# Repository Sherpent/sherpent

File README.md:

# Sherpent – Équipe #3
## S.H.E.R.P.E.N.T.
Système
Hybride
Exploratoire
Robotique
Prototypé
Et
Navigation
Tout-terrain

## 🌐 Projet: Sherpent – Robot Tout-Terrain Inspiré des Serpents

**Membres de l'équipe :**
- **Nathan Lachapelle** (lacn1101)
- **Émile Raymond** (raye1901)
- **Gabriel Grondin** (grog1401)
- **Mathieu Durand** (durm1207)
- **Renaud Gagnon** (gegr1618)
- **Maxime Boucher** (boom0704)

---

## 🔬 Contexte

Le projet Sherpent vise à concevoir et prototyper un véhicule tout-terrain s’inspirant des mouvements ondulatoires d’un serpent pour se déplacer. Les serpents utilisent leurs centaines de vertèbres et leurs muscles pour glisser sur diverses surfaces (‎terre, bois, vitre, sable, etc.), ce qui leur confère une capacité passe-partout. Ce type de locomotion est idéal pour des missions d’exploration terrestre ou pour évoluer dans des environnements extraterrestres hostiles.

L'étude des mouvements naturels de ces reptiles servira de base à la conception du robot Sherpent.

---

## 🎯 Objectifs du Projet

- **Robot articulé :** Le robot comprendra des joints articulés permettant des mouvements ondulatoires.
- **Actionneurs et capteurs :** Intégration d’actionneurs et de capteurs pour permettre un contrôle précis des mouvements.
- **Contrôle autonome :** Le robot fonctionnera de manière autonome, sans dépendance à des fils ou sources externes.
- **Langage Python :** Utilisation de Python pour une partie du code contrôlant le robot.
- **Applications potentielles :** Exploration terrestre ou exploration d’environnements extraterrestres.

---

## 📅 Livrables Attendues
Le projet sera développé en utilisant la méthodologie Agile, avec des livrables majeurs prévus à la fin de chaque sprint de 3 semaines :

| **Dates**           | **Livrables Importants**                  |
|---------------------|------------------------------------------|
| 22 janvier 2025     | Preuve de concept simple                |
| 12 février 2025    | PCB montés et débuggés                 |
| 26 février 2025    | Contrôle du prototype                  |
| 26 mars 2025        | Phase de test du prototype              |
| 11 avril 2025       | Rapport et prototype final              |

---

## 📊 Analyse Sommaire de Faisabilité

**Compétences :** L’équipe possède une expertise multidisciplinaire en robotique :
- Compétences en électronique, mécanique et informatique.

**Ressources matérielles :** 
- Accès à du matériel et des installations telles que machines-outils, composants électroniques, et équipements de prototypage.

**Budget :** Les coûts supplémentaires seront partagés ou répartis selon les membres qui conserveront les matériaux au terme du projet.

**Conclusion :** Compte tenu des compétences, du matériel disponible et des ressources temporelles, l’équipe juge ce projet réalisable dans les délais impartis.

---

## 🔄 Planification Sommaire

1. **Organisation de l’équipe :**
   - Division en trois sections : électrique, mécanique, et informatique.
   - Collaboration interdépendante pour surmonter les embûches.

2. **Gestion de Projet :**
   - Utilisation de GitHub pour gérer le code, les fichiers, et la planification.
   - Réunion hebdomadaire chaque mercredi pour faire le point sur les avancements et problèmes.

3. **Développement Agile :**
   - Livrables précis à la fin de chaque sprint de 3 semaines.

---

## 🔧 Utilisation de GitHub

1. **Structure du Répertoire :**
   ```
   Sherpent/
   ├── elec/       # Fichiers électroniques (PCB, schémas, etc.)
   ├── mec/        # Fichiers mécaniques (CAD, modèles 3D, etc.)
   ├── code/       # Fichiers de code (Python, firmware, etc.)
   └── docs/       # Documentation et rapports
   ```

2. **Outils GitHub :**
   - **Issues :** Pour suivre les problèmes et défis.
   - **Projets :** Pour gérer les tâches et la planification Agile.
   - **Pull Requests :** Pour réviser et intégrer les changements.

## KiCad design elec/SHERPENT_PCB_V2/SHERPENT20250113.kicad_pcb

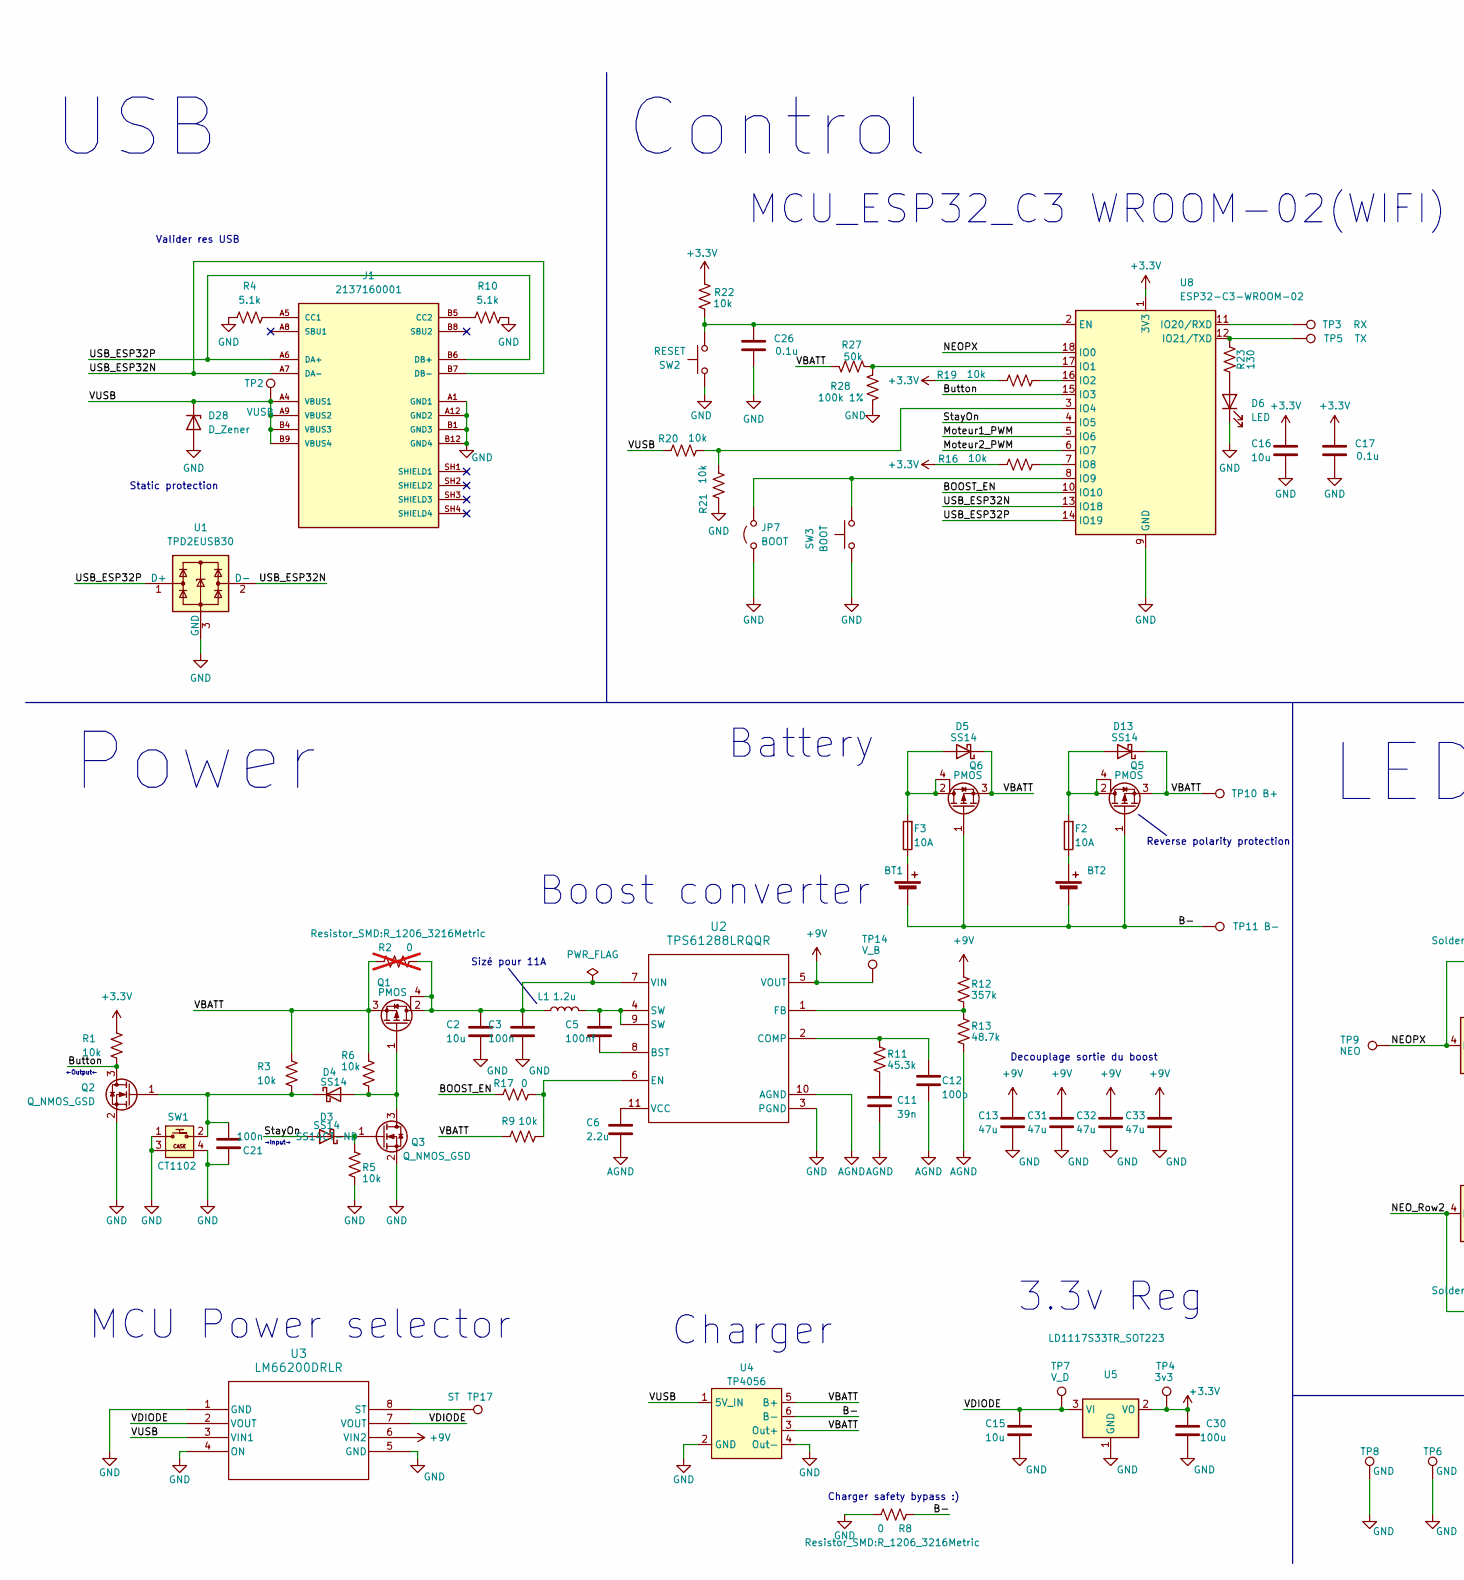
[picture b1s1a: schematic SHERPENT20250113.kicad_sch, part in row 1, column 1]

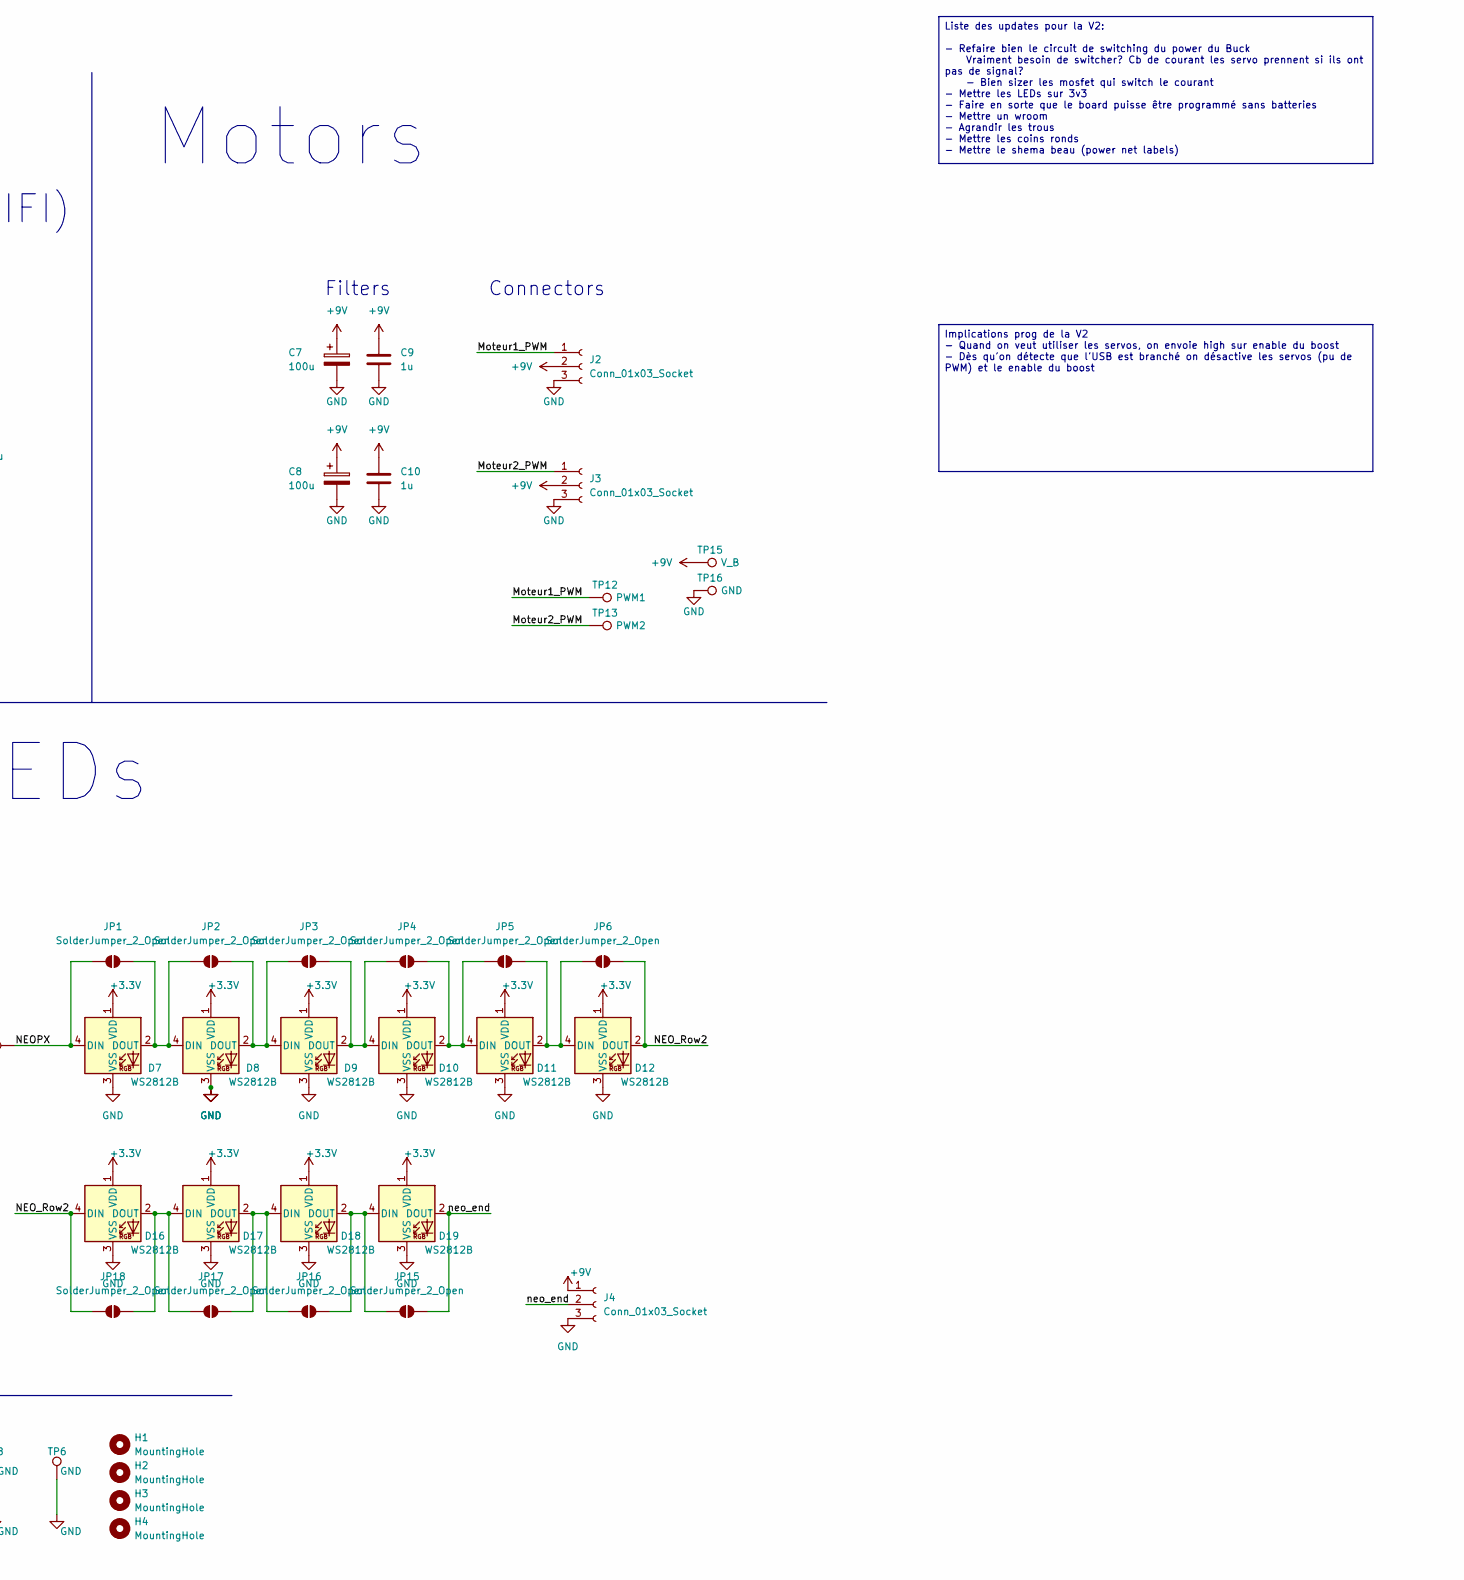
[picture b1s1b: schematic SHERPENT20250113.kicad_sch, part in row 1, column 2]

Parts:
BT1, BT2: Battery_Cell; PinHeader_1x02_P2.54mm_Vertical
C2, C15, C16: 10u; C_0603_1608Metric_Pad1.08x0.95mm_HandSolder
C3, C21: 100n; C_0603_1608Metric_Pad1.08x0.95mm_HandSolder
C5: 100nf; C_0603_1608Metric_Pad1.08x0.95mm_HandSolder
C6: 2.2u; C_0603_1608Metric_Pad1.08x0.95mm_HandSolder
C7, C8: 100u; CP_Radial_D5.0mm_P2.00mm
C9, C10: 1u; C_0603_1608Metric_Pad1.08x0.95mm_HandSolder
C11: 39n; C_0603_1608Metric_Pad1.08x0.95mm_HandSolder
C12: 100p; C_0603_1608Metric_Pad1.08x0.95mm_HandSolder
C13, C31, C32, C33: 47u; C_0603_1608Metric_Pad1.08x0.95mm_HandSolder
C17, C26: 0.1u; C_0603_1608Metric_Pad1.08x0.95mm_HandSolder
C30: 100u; C_0603_1608Metric_Pad1.08x0.95mm_HandSolder
D3, D4, D5, D13: SS14; D_SMA; DigiKey SS14CT-ND
D6: LED; LED_0603_1608Metric_Pad1.05x0.95mm_HandSolder
D7: WS2812B; LED_WS2812B_PLCC4_5.0x5.0mm_P3.2mm; MPN WS2812B-5050
D8, D9, D10, D11, D12, D16, D17, D18, D19: WS2812B; LED_WS2812B_PLCC4_5.0x5.0mm_P3.2mm
D28: D_Zener; R_0603_1608Metric_Pad0.98x0.95mm_HandSolder
F2, F3: 10A; Fuse_0603_1608Metric
H1, H2, H3, H4: MountingHole; MountingHole_3.2mm_M3
J1: 2137160001; MOLEX_2137160001; PARTREV B
J2, J3, J4: Conn_01x03_Socket; PinHeader_1x03_P2.54mm_Vertical
JP1, JP2, JP3, JP4, JP5, JP6, JP15, JP16, JP17, JP18: SolderJumper_2_Open; SolderJumper-2_P1.3mm_Open_TrianglePad1.0x1.5mm
JP7: BOOT; PinHeader_1x02_P2.54mm_Vertical
L1: 1.2u; IND_CMLE105T-1R0&slash_1R5&slash_2R2_CYN; DigiKey 2037-CMLE105T-1R0MSCT-ND
Q1, Q5, Q6: PMOS; SOT-223; MPN NTF6P02T3G; DigiKey 3141-G170P06MCT-ND
Q2, Q3: Q_NMOS_GSD; SOT-23; MPN SN7002NH6433XTMA1; DigiKey 448-SN7002NH6433XTMA1CT-ND
R1, R3, R5, R6, R9, R16, R19, R20, R21, R22: 10k; R_0603_1608Metric
R2: 0; R_1206_3216Metric; not fitted
R4, R10: 5.1k; R_0603_1608Metric
R8: 0; R_1206_3216Metric
R11: 45.3k; R_0603_1608Metric
R12: 357k; R_0603_1608Metric
R13: 48.7k; R_0603_1608Metric
R17: 0; R_0603_1608Metric
R23: 130; R_0603_1608Metric
R27: 50k; R_0603_1608Metric
R28: 100k 1%; R_0603_1608Metric
SW1: CT1102; CT1102V3.15F100
SW2: RESET; SW_CS1213AG_CRS
SW3: BOOT; SW_CS1213AG_CRS
TP2: VUSB; TestPoint_Loop_D2.54mm_Drill1.5mm_Beaded
TP3: RX; TestPoint_Loop_D2.54mm_Drill1.5mm_Beaded
TP4: 3v3; TestPoint_Loop_D2.54mm_Drill1.5mm_Beaded
TP5: TX; TestPoint_Loop_D2.54mm_Drill1.5mm_Beaded
TP6, TP8, TP16: GND; TestPoint_Loop_D2.54mm_Drill1.5mm_Beaded
TP7: V_D; TestPoint_Loop_D2.54mm_Drill1.5mm_Beaded
TP9: NEO; TestPoint_Loop_D2.54mm_Drill1.5mm_Beaded
TP10: B+; TestPoint_Loop_D2.54mm_Drill1.5mm_Beaded
TP11: B-; TestPoint_Loop_D2.54mm_Drill1.5mm_Beaded
TP12: PWM1; TestPoint_Loop_D2.54mm_Drill1.5mm_Beaded
TP13: PWM2; TestPoint_Loop_D2.54mm_Drill1.5mm_Beaded
TP14, TP15: V_B; TestPoint_Loop_D2.54mm_Drill1.5mm_Beaded
TP17: ST; TestPoint_Loop_D2.54mm_Drill1.5mm_Beaded
U1: TPD2EUSB30; Texas_DRT-3
U2: TPS61288LRQQR; RQQ0011A-MFG; MPN TPS61288LRQQR; DigiKey 296-TPS61288LRQQRCT-ND
U3: LM66200DRLR; SOT-5X3_DRL_TEX-L
U4: TP4056; TP4056-18650
U5: LD1117S33TR_SOT223; SOT-223-3_TabPin2
U8: ESP32-C3-WROOM-02

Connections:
+3.3V: C16.1, C17.1, C30.2, D7.1 (VDD), D8.1 (VDD), D9.1 (VDD), D10.1 (VDD), D11.1 (VDD), D12.1 (VDD), D16.1 (VDD), D17.1 (VDD), D18.1 (VDD), D19.1 (VDD), R1.1, R16.1, R19.1, R22.2, TP4.1, U5.2 (VO), U8.1 (3V3)
+9V: C7.1, C8.1, C9.1, C10.1, C13.1, C31.1, C32.1, C33.1, J2.2, J3.2, J4.1, R12.1, TP14.1, TP15.1, U2.5 (VOUT), U3.6 (VIN2)
/B-: BT1.2 (-), BT2.2 (-), Q5.1 (G), Q6.1 (G), R8.1, TP11.1, U4.6 (B-)
/BOOST_EN: R17.1, U8.10 (IO10)
/Button: Q2.3 (D), R1.2, U8.15 (IO3)
/Moteur1_PWM: J2.1, TP12.1, U8.5 (IO6)
/Moteur2_PWM: J3.1, TP13.1, U8.6 (IO7)
/NEOPX: D7.4 (DIN), JP1.1 (A), TP9.1, U8.18 (IO0)
/NEO_Row2: D12.2 (DOUT), D16.4 (DIN), JP6.2 (B), JP18.1 (A)
/StayOn: D3.2 (A), U8.4 (IO5)
/USB_ESP32N: J1.A7 (DA-), J1.B7 (DB-), U1.2 (D-), U8.13 (IO18)
/USB_ESP32P: J1.A6 (DA+), J1.B6 (DB+), U1.1 (D+), U8.14 (IO19)
/VBATT: D5.1 (K), D13.1 (K), Q1.3 (S), Q5.3 (S), Q6.3 (S), R2.1, R3.1, R6.1, R9.1, R27.2, TP10.1, U4.3 (Out+), U4.5 (B+)
/VDIODE: C15.1, TP7.1, U3.2 (VOUT), U3.7 (VOUT), U5.3 (VI)
/VUSB: D28.1 (K), J1.A4 (VBUS1), J1.A9 (VBUS2), J1.B4 (VBUS3), J1.B9 (VBUS4), R20.1, TP2.1, U3.3 (VIN1), U4.1 (5V_IN)
/neo_end: D19.2 (DOUT), J4.2, JP15.2 (B)
AGND: C6.2, C11.2, C12.2, R13.2, U2.10 (AGND)
GND: C2.2, C3.2, C7.2, C8.2, C9.2, C10.2, C13.2, C15.2, C16.2, C17.2, C21.1, C26.2, C30.1, C31.2, C32.2, C33.2, D6.1 (K), D7.3 (VSS), D8.3 (VSS), D9.3 (VSS), D10.3 (VSS), D11.3 (VSS), D12.3 (VSS), D16.3 (VSS), D17.3 (VSS), D18.3 (VSS), D19.3 (VSS), D28.2 (A), J1.A1 (GND1), J1.A12 (GND2), J1.B1 (GND3), J1.B12 (GND4), J2.3, J3.3, J4.3, JP7.1 (A), Q2.2 (S), Q3.2 (S), R4.1, R5.2, R8.2, R10.2, R21.1, R28.1, SW1.1, SW1.3, SW1.4, SW2.1, SW3.1, TP6.1, TP8.1, TP16.1, U1.3 (GND), U2.3 (PGND), U3.1 (GND), U3.4 (ON), U3.5 (GND), U4.2 (GND), U4.4 (Out-), U5.1 (GND), U8.9 (GND), U8.19 (GND)
unnamed: BT1.1 (+), F3.1
unnamed: BT2.1 (+), F2.1
unnamed: C5.1, L1.2, U2.4 (SW), U2.9 (SW)
unnamed: C11.1, R11.2
unnamed: D3.1 (K), Q3.1 (G), R5.1
unnamed: D4.2 (A), Q1.1 (G), Q3.3 (D), R6.2
unnamed: C21.2, D4.1 (K), Q2.1 (G), R3.2, SW1.2
unnamed: D5.2 (A), F3.2, Q6.2 (D), Q6.4 (D)
unnamed: D6.2 (A), R23.1
unnamed: D7.2 (DOUT), D8.4 (DIN), JP1.2 (B), JP2.1 (A)
unnamed: D8.2 (DOUT), D9.4 (DIN), JP2.2 (B), JP3.1 (A)
unnamed: D9.2 (DOUT), D10.4 (DIN), JP3.2 (B), JP4.1 (A)
unnamed: D10.2 (DOUT), D11.4 (DIN), JP4.2 (B), JP5.1 (A)
unnamed: D11.2 (DOUT), D12.4 (DIN), JP5.2 (B), JP6.1 (A)
unnamed: D13.2 (A), F2.2, Q5.2 (D), Q5.4 (D)
unnamed: D16.2 (DOUT), D17.4 (DIN), JP17.1 (A), JP18.2 (B)
unnamed: D17.2 (DOUT), D18.4 (DIN), JP16.1 (A), JP17.2 (B)
unnamed: D18.2 (DOUT), D19.4 (DIN), JP15.1 (A), JP16.2 (B)
unnamed: J1.A5 (CC1), R4.2
unnamed: J1.B5 (CC2), R10.1
unnamed: JP7.2 (B), SW3.2, U8.8 (IO9)
unnamed: C5.2, U2.8 (BST)
unnamed: C12.1, R11.1, U2.2 (COMP)
unnamed: R9.2, R17.2, U2.6 (EN)
unnamed: R12.2, R13.1, U2.1 (FB)
unnamed: C6.1, U2.11 (VCC)
unnamed: C2.1, C3.1, L1.1, Q1.2 (D), Q1.4 (D), R2.2, U2.7 (VIN)
unnamed: TP17.1, U3.8 (ST)
unnamed: C26.1, R22.1, SW2.2, U8.2 (EN)
unnamed: R27.1, R28.2, U8.17 (IO1)
unnamed: R19.2, U8.16 (IO2)
unnamed: R20.2, R21.2, U8.3 (IO4)
unnamed: R16.2, U8.7 (IO8)
unnamed: TP3.1, U8.11 (IO20/RXD)
unnamed: R23.2, TP5.1, U8.12 (IO21/TXD)

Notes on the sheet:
Reverse polarity protection
LEDs
3.3v Reg
Filters
Sizé pour 11A
Control
Battery
Static protection
←Output←
Decouplage sortie du boost
Boost converter
MCU_ESP32_C3 WROOM-02(WIFI)
Charger safety bypass :)
Valider res USB
USB
Connectors
Motors
MCU Power selector
Power
Charger
→Input→
Liste des updates pour la V2: - Refaire bien le circuit de switching du power du Buck Vraiment besoin de switcher? Cb de courant les servo prennent si ils ont pas de signal? - Bien sizer les mosfet qui switch le courant - Mettre les LEDs sur 3v3 - Faire en sorte que le board puisse être programmé s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
Implications prog de la V2 - Quand on veut utiliser les servos, on envoie high sur enable du boost - Dès qu'on détecte que l'USB est branché on désactive les servos (pu de PWM) et le enable du boost

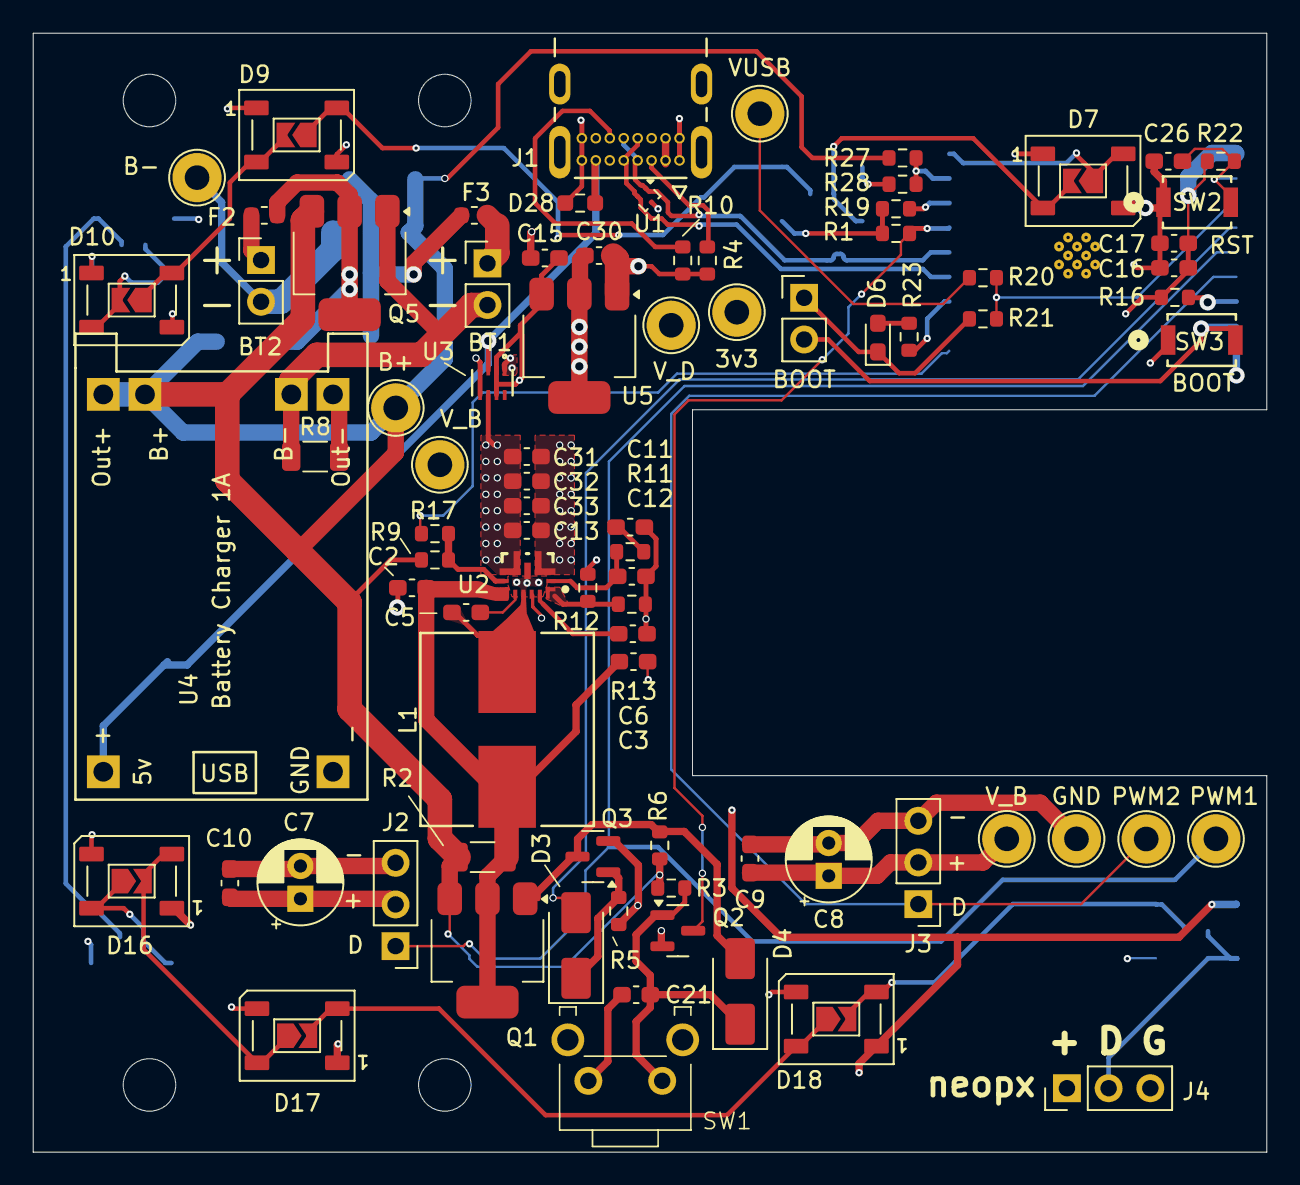
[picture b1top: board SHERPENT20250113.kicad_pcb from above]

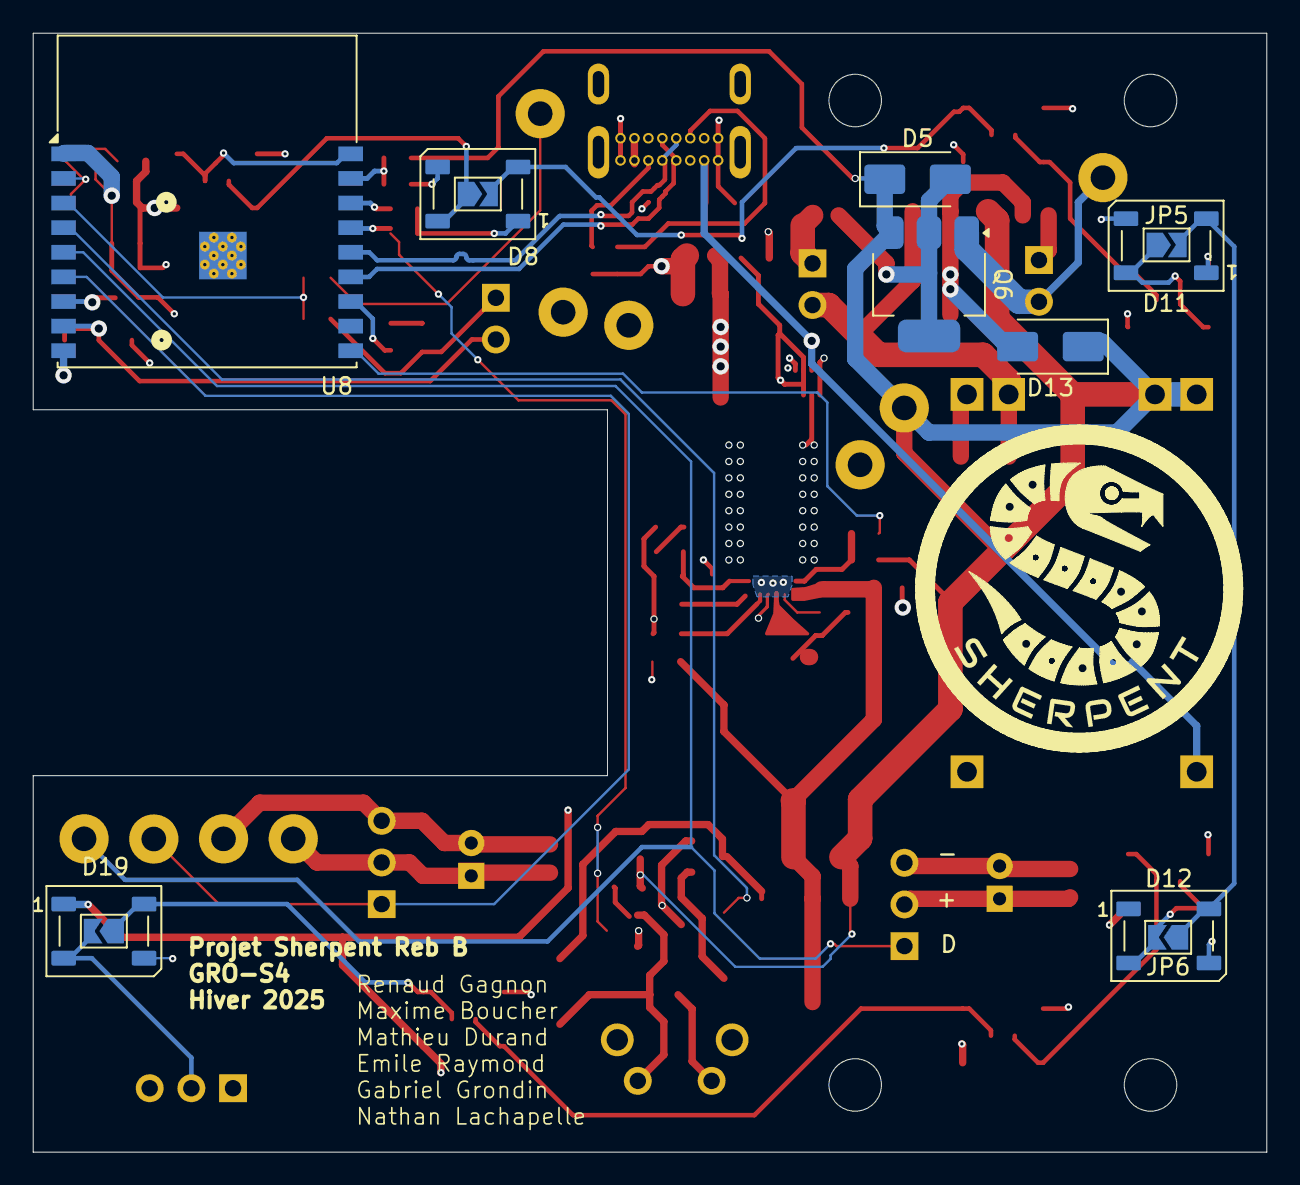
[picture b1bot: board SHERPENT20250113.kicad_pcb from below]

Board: 4 copper layers, 75.2 x 68.2 mm, 105 parts (12 on the bottom side), 51 nets.

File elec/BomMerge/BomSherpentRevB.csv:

"Reference","Value","Footprint","Qty","DigiKey"
"BT1,BT2","Battery_Cell","Connector_PinHeader_2.54mm:PinHeader_1x02_P2.54mm_Vertical","2",""
"C2,C15,C16","10u","Capacitor_SMD:C_0603_1608Metric_Pad1.08x0.95mm_HandSolder","3","587-1256-1-ND"
"C3,C5,C21","100n","Capacitor_SMD:C_0603_1608Metric_Pad1.08x0.95mm_HandSolder","3","311-1344-1-ND"
"C7,C8","100u","Capacitor_THT:CP_Radial_D5.0mm_P2.00mm","2","732-8793-1-ND"
"C9,C10","1u","Capacitor_SMD:C_0603_1608Metric_Pad1.08x0.95mm_HandSolder","2","587-1248-1-ND"
"C11","39n","Capacitor_SMD:C_0603_1608Metric_Pad1.08x0.95mm_HandSolder","1","1276-2055-1-ND"
"C12","100p","Capacitor_SMD:C_0603_1608Metric_Pad1.08x0.95mm_HandSolder","1","490-4771-1-ND"
"C13,C31,C32,C33","47u","Capacitor_SMD:C_0603_1608Metric_Pad1.08x0.95mm_HandSolder","4","1276-1852-1-ND"
"C17,C26","0.1u","Capacitor_SMD:C_0603_1608Metric_Pad1.08x0.95mm_HandSolder","2","311-1344-1-ND"
"C30","100u","Capacitor_SMD:C_0603_1608Metric_Pad1.08x0.95mm_HandSolder","1","490-GRM21BR60G107ME11KCT-ND"
"D3,D4,D5,D13","SS14","Diode_SMD:D_SMA","4","SS14CT-ND"
"D7,D8,D9,D10,D11,D12,D16,D17,D18,D19","WS2812B","LED_SMD:LED_WS2812B_PLCC4_5.0x5.0mm_P3.2mm","10",""
"F2,F3","10A","Fuse:Fuse_0603_1608Metric","2","5923-0686F8000-01CT-ND"
"J1","2137160001","2137160001:MOLEX_2137160001","1","2073-USB4085-GF-ACT-ND"
"J2,J3,J4","Conn_01x03_Socket","Connector_PinHeader_2.54mm:PinHeader_1x03_P2.54mm_Vertical","3",""
"JP7","BOOT","Connector_PinHeader_2.54mm:PinHeader_1x02_P2.54mm_Vertical","1",""
"L1","1.2u","CMLE105T-2R2MS:IND_CMLE105T-1R0&slash_1R5&slash_2R2_CYN","1","2037-CMLE105T-1R0MSCT-ND"
"Q1,Q5,Q6","PMOS","Package_TO_SOT_SMD:SOT-223","3","3141-G170P06MCT-ND"
"Q2,Q3","Q_NMOS_GSD","Package_TO_SOT_SMD:SOT-23","2","448-SN7002NH6433XTMA1CT-ND"
"R1,R3,R5,R6,R9,R16,R19,R20,R21,R22","10k","Resistor_SMD:R_0603_1608Metric","10","311-5.10KHRCT-ND"
"R4,R10","5.1k","Resistor_SMD:R_0603_1608Metric","2","311-5.10KHRCT-ND"
"R11","45.3k","Resistor_SMD:R_0603_1608Metric","1","311-45.3KHRCT-ND"
"R12","357k","Resistor_SMD:R_0603_1608Metric","1","311-357KHRCT-ND"
"R13","48.7k","Resistor_SMD:R_0603_1608Metric","1","311-48.7KHRCT-ND"
"R17","0","Resistor_SMD:R_0603_1608Metric","1","311-0.0GRCT-ND"
"R27","50k","Resistor_SMD:R_0603_1608Metric","1","13-RT0603BRD0750KLCT-ND"
"R28","100k 1%","Resistor_SMD:R_0603_1608Metric","1","P100KHCT-ND"
"SW1","CT1102","CT1102V3.15F100:CT1102V3.15F100","1","2449-CT1102V3.15F100-ND"
"SW2","RESET","CS1213AGF160:SW_CS1213AG_CRS","1","2449-CS1213AGF260CT-ND"
"SW3","BOOT","CS1213AGF160:SW_CS1213AG_CRS","1","2449-CS1213AGF260CT-ND"
"TP2","VUSB","TestPoint:TestPoint_Loop_D2.54mm_Drill1.5mm_Beaded","1",""
"TP3","RX","TestPoint:TestPoint_Loop_D2.54mm_Drill1.5mm_Beaded","1",""
"TP4","3v3","TestPoint:TestPoint_Loop_D2.54mm_Drill1.5mm_Beaded","1",""
"TP5","TX","TestPoint:TestPoint_Loop_D2.54mm_Drill1.5mm_Beaded","1",""
"TP6,TP8,TP16","GND","TestPoint:TestPoint_Loop_D2.54mm_Drill1.5mm_Beaded","3",""
"TP7","V_D","TestPoint:TestPoint_Loop_D2.54mm_Drill1.5mm_Beaded","1",""
"TP9","NEO","TestPoint:TestPoint_Loop_D2.54mm_Drill1.5mm_Beaded","1",""
"TP10","B+","TestPoint:TestPoint_Loop_D2.54mm_Drill1.5mm_Beaded","1",""
"TP11","B-","TestPoint:TestPoint_Loop_D2.54mm_Drill1.5mm_Beaded","1",""
"TP12","PWM1","TestPoint:TestPoint_Loop_D2.54mm_Drill1.5mm_Beaded","1",""
"TP13","PWM2","TestPoint:TestPoint_Loop_D2.54mm_Drill1.5mm_Beaded","1",""
"TP14,TP15","V_B","TestPoint:TestPoint_Loop_D2.54mm_Drill1.5mm_Beaded","2",""
"TP17","ST","TestPoint:TestPoint_Loop_D2.54mm_Drill1.5mm_Beaded","1",""
"U1","TPD2EUSB30","Package_TO_SOT_SMD:Texas_DRT-3","1","296-28153-1-ND"
"U2","TPS61288LRQQR","TPS61288LRQQR:RQQ0011A-MFG","1","296-TPS61288LRQQRCT-ND"
"U3","LM66200DRLR","LM66200DRLR:SOT-5X3_DRL_TEX-L","1","296-LM66200DRLRCT-ND"
"U4","TP4056","TP4056:TP4056-18650","1",""
"U5","LD1117S33TR_SOT223","Package_TO_SOT_SMD:SOT-223-3_TabPin2","1","497-1241-1-ND"
"U8","ESP32-C3-WROOM-02","RF_Module:ESP32-C3-WROOM-02","1","1965-ESP32-C3-WROOM-02-N4CT-ND"

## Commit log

2025-01-13 Structure de dossiers
2025-01-13 Create README.md
    merci chat ;)
2025-01-13 structure de données selon readme
2025-01-13 Début du pcb
2025-01-15 Changement du DCDC pour quelque chose qui fit avec le servo
2025-01-15 Ajout du circuit du buck-boost
2025-01-22 Finalisation du schematics pre-révision
2025-01-22 Début du layout
2025-01-22 Oublier de save
2025-01-22 Rename readme.md to README.md
2025-01-22 Initializing platformio
2025-01-22 Layout: circuit ESP finalisé + début du circuit buck-boost
2025-01-22 Auto stash before merge of "main" and "origin/main"
2025-01-22 chu pas sur de ce que je fais live
2025-01-22 Added pcb outline and gitignore
2025-01-22 fini pour ajd
2025-01-23 Réparation d'erreur
2025-01-25 Avancement du circuit des batteries et de contrôle
2025-01-26 Ajout des LED sur le pcb
2025-01-26 Ajout de step
2025-01-27 Changer le connecteur usb de côté
2025-01-27 Keepout
2025-01-27 rough rgb placement
2025-01-27 Quicksave. J'ai mis le connecteur du bon bord. Va falloir flipper le trou de place pis recheck le routing. Stayon circuit en cours
2025-01-27 StayOn supposé être fonctionnel
2025-01-28 shema bo
2025-01-28 Amélioration du shema. Layout et routing de tout ce qui manquait sauf leds et bouton. Bonne nuit!
2025-01-29 Segment project ESP-IDF setup
2025-01-29 Communication module containing struct used for standardized messaging between modules
2025-01-29 First implementation based on BLE exemple, responding to log (Structure defined on module communication.h in schemas) message on characteristic UUID:FF01 of device ESP_GATT_DEMO
2025-01-29 Ajout de datasheet et changement de LDO
2025-01-29 Bouton :)
2025-01-29 Server code refactor (Splitting into multiples files and cleaning of variables and functions definitions)
2025-01-29 Fixing CMake (replace duplicate head.c by server.c)
2025-01-29 Bouton placé
2025-01-30 Tiens max have fun
2025-01-30 Adversiting (Server) and Scanning/Connecting (Client) as the same time
2025-01-30 Changement de place de l'ESP
2025-01-30 Including MAC address in the device name turn's out to not be useful
2025-01-30 PCB finie, il reste le DRC
2025-01-31 Vérification de la charge des batterie et début du sizing des via/track
2025-01-31 Mise à jour des netclass
2025-01-31 Sauvegarde pre-tutorat
2025-01-31 Ajout du thermal relief sur le buck dcdc converter
2025-02-01 Modification simple sur la layout, buck-boost
2025-02-01 Ajout de la lecture de tension des cellules, grosseur des track, intégrité des signaux
2025-02-04 Pascal was here
2025-02-04 Petites modifs pour le 4mm 3d et export step
2025-02-05 DRC ok
2025-02-05 sleep? no! PCB!
2025-02-05 qqch
    oui
2025-02-05 Vite! Mon lit m'attend!
2025-02-05 Committing my most recent changes
2025-02-05 Vérification
2025-02-05 Changement des cap pour des electrolotique
2025-02-05 Fix so Gab can work
2025-02-05 Renaud, prend le lead
2025-02-05 b- != gnd
2025-02-05 Text editor = kicad editor?
2025-02-05 this device complies with part 15 of the fcc rules
    amongoose
2025-02-05 Silkscreen done
2025-02-06 done
2025-02-06 moi quand ta mere
2025-02-06 liafubsdkgmasa
2025-02-06 Conn neopx
2025-02-06 Gerber générés et PCB envoyé pour la fabrication
2025-02-06 ajout du gerber.zip
2025-02-11 Creation Dossier UI
2025-02-11 Debut du UI
2025-02-11 Modification du gitignore
2025-02-11 Ajout d'une liste de truc à améliorer pour la mec
2025-02-11 Step board cutté
2025-02-11 Truc fait en mec
2025-02-11 Multiples services!! Finally
2025-02-11 Mini simulation de l'affichage du Sherpent
2025-02-12 Fix service advertisement
2025-02-12 Added header file for head.c file
2025-02-12 Advertising & Scan basic closures and methods
2025-02-12 Client & Server, connection and disconnection events
2025-02-12 Untested connect_device method to Connect to another module
2025-02-13 modification du protocole de test
2025-02-19 Handling address types in connections
2025-02-19 Disconnection functions
2025-02-19 Handling scan results events
2025-02-19 Receiving messages from front and back handled
2025-02-19 Handling extra closure in ble_main
2025-02-19 More general on_message support
2025-02-19 Integration de la sim au UI
2025-02-19 Removed auto start scanning and start advertising
2025-02-19 First testing
2025-02-19 New Branch For Dev
2025-02-19 updated cmake
2025-02-19 Here we go again
2025-02-19 Corrected sdk config
2025-02-19 Ca marche sur une de bord?
2025-02-20 Continue UI
2025-02-20 Structure changes
2025-02-20 Fixed structure changes
2025-02-20 Commit Message
2025-02-20 Fixed ble.h of head
2025-02-20 First iteration of the body code
2025-02-20 Ca marche
2025-02-20 started cleaning ble shit
2025-02-25 Sherpent's custom PCB library
2025-02-25 Fixing import in sherpent.c
2025-02-25 Adding nvs flash to required libs
2025-02-25 Cleanup
2025-02-25 Cleanup v2...
2025-02-25 Remove multiples profile code in favor of a single profile
2025-02-25 Snall cleanup
2025-02-25 Small cleanup
2025-02-25 Patches à faire (todo)
2025-02-25 Callbacks and message handling + sending
2025-02-25 More callback and advertising control
2025-02-25 Removed unused
2025-02-25 Explication détaillée des patches
2025-02-26 Bluetooth server side working!!!!!
2025-02-26 Reworked communication schema and implemented basic response to message
2025-02-26 Effect layering with main color support
2025-02-26 Led function order reorganization
2025-02-28 Actually working effect stack + breathing effect
2025-03-02 Essaies controles avec manette de PS4
2025-03-12 More cleanup
2025-03-12 Safety Managing (Battery voltage limits)
2025-03-12 Ignore ESP-IDF folder
2025-03-12 Make sure inits are only called once
2025-03-12 UI_V3: Control du sherpent avec la manette en sim
2025-03-12 ShemaBloc
2025-03-12 Commit power and safety fix
2025-03-19 Final transition to ESP_IDF 5.4v and handling connection from a "master" client
2025-03-19 Actual configuration file
2025-03-19 Debug servo undervoltage (brownout)
2025-03-24 Debug mosfet de switching de power
2025-03-24 Servo test
2025-03-25 amogus
2025-03-25 Untested client side code
2025-03-25 Notes
2025-03-26 balls
2025-03-26 More notes
2025-03-26 Module communication working
2025-03-26 Automatic reconnection + Permanent segment id in memory
2025-03-26 Communicate with modules properly
2025-03-27 ShemaV2 1st stretch
2025-03-27 ShemaV2Fini
2025-03-27 pcb V2 commencé
2025-03-27 Auto stash before merge of "PCB_V2" and "origin/PCB_V2"
2025-03-27 Added a extra check
2025-03-27 Improved segment code
2025-03-27 Moved code to reduce issues
2025-03-27 Updated the CMakes
2025-03-27 Added struct for controlling the robot as a master
2025-03-27 Avancer PCB
2025-03-28 routing done. Good night.
2025-03-28 Ajout bluetooth thread
2025-03-28 Reste le silkscreen
2025-03-29 Commandé
2025-03-29 Step
2025-03-29 Remis la revA dans le repos
2025-03-29 Com bluetooth avec Sherpent
2025-03-29 Msg received from bluetooth
2025-04-01 Retrait partie inutile du README
2025-04-02 Buffer angles so that they can be set before modules are connected + Communication with computer
2025-04-02 Roll into a ball on power up
2025-04-02 Intégration de la classe bluetooth
2025-04-02 Movement queue and look up function
2025-04-04 Notes patch v1
2025-04-04 plus vite
2025-04-04 notes de debug. Boards 2,3,4 ont passé le test moteur
2025-04-09 Patch Note
2025-04-09 ajouté les part numbers dasn revA
2025-04-09 ajouté les part numbers dans revB
2025-04-09 Modif UI
2025-04-09 CommandeDigikey
2025-04-09 Com controle bluetooth fonctionnelle
2025-04-10 A lot!!!!!
2025-04-10 Message for sending both yaw and pitch at the same times
2025-04-10 Beautiful UI
2025-04-10 UI-more beautiful
2025-04-11 Correction d'erreur sur le schéma
2025-04-11 v2 pinout
2025-04-11 UI presque final
2025-04-11 Everything
2025-04-12 UI final
2025-04-12 Clean up code UI
